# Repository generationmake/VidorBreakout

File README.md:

# VidorBreakout
Breakout board for the Mini PCIe connector of the Arduino MKR Vidor 4000.

## PCB

### Top

### Bot

## License

This hardware is licensed under the CERN OHL v. 1.2

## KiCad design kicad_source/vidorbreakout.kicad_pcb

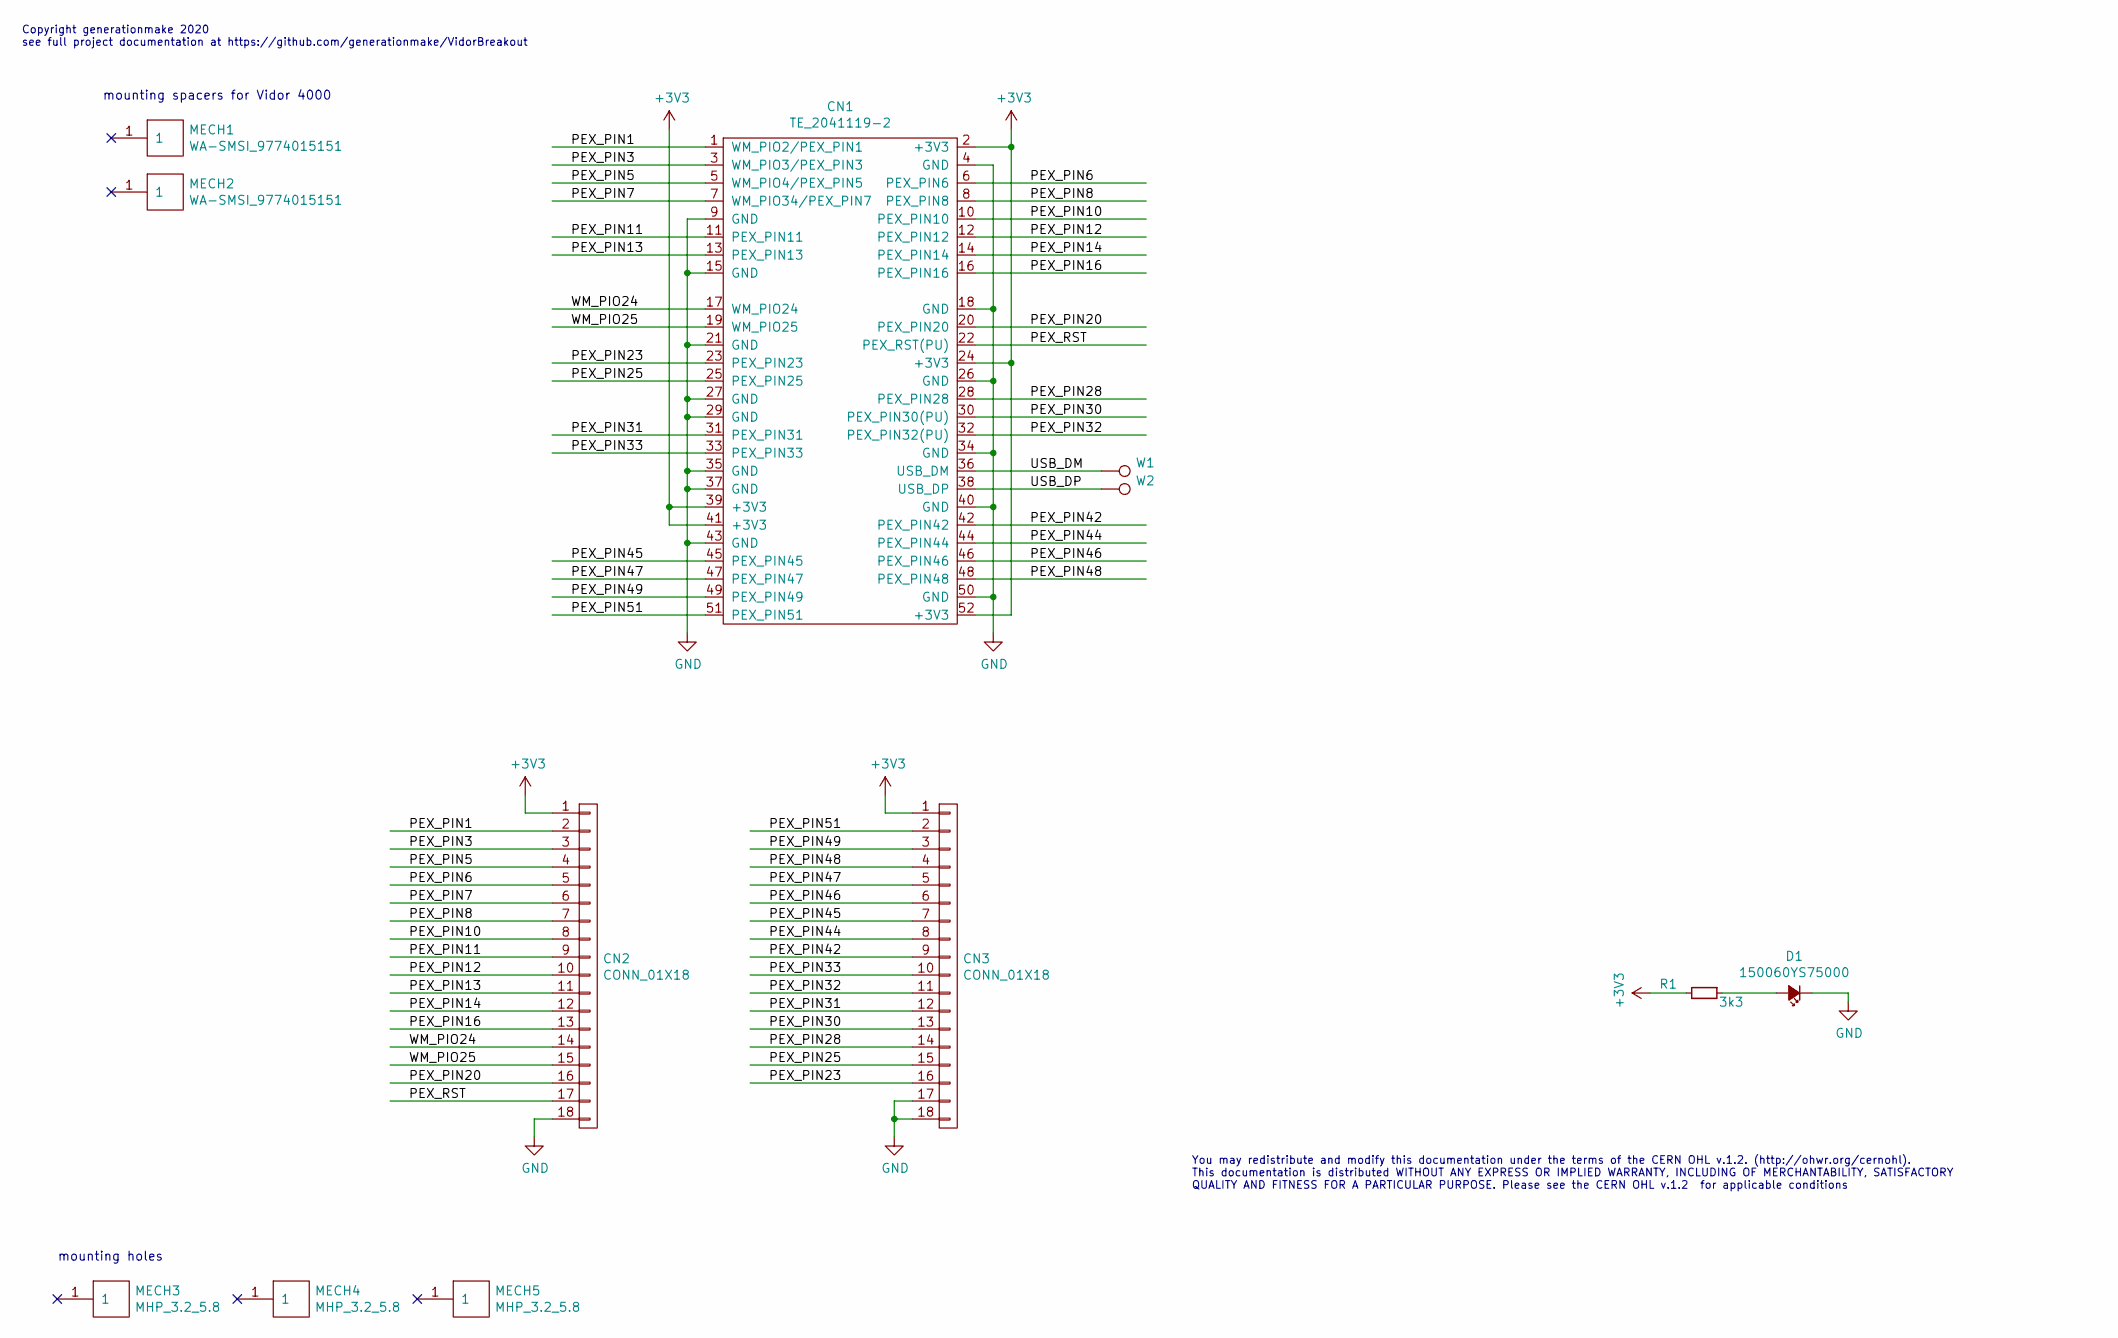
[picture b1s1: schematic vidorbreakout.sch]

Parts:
CN1: TE_2041119-2; MPCIe_4mm
CN2, CN3: CONN_01X18; Pin_Header_Straight_1x18
D1: 150060YS75000; LED_0603
MECH1, MECH2: WA-SMSI_9774015151
MECH3, MECH4, MECH5: MHP_3.2_5.8
R1: 3k3; R_0603
W1, W2: TEST_1P; SolderWirePad_single_1mmSMD

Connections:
+3V3: CN1.2 (+3V3), CN1.24 (+3V3), CN1.39 (+3V3), CN1.41 (+3V3), CN1.52 (+3V3), CN2.1, CN3.1, R1.2
/PEX_PIN1: CN1.1 (WM_PIO2/PEX_PIN1), CN2.2
/PEX_PIN3: CN1.3 (WM_PIO3/PEX_PIN3), CN2.3
/PEX_PIN5: CN1.5 (WM_PIO4/PEX_PIN5), CN2.4
/PEX_PIN6: CN1.6 (PEX_PIN6), CN2.5
/PEX_PIN7: CN1.7 (WM_PIO34/PEX_PIN7), CN2.6
/PEX_PIN8: CN1.8 (PEX_PIN8), CN2.7
/PEX_PIN10: CN1.10 (PEX_PIN10), CN2.8
/PEX_PIN11: CN1.11 (PEX_PIN11), CN2.9
/PEX_PIN12: CN1.12 (PEX_PIN12), CN2.10
/PEX_PIN13: CN1.13 (PEX_PIN13), CN2.11
/PEX_PIN14: CN1.14 (PEX_PIN14), CN2.12
/PEX_PIN16: CN1.16 (PEX_PIN16), CN2.13
/PEX_PIN20: CN1.20 (PEX_PIN20), CN2.16
/PEX_PIN23: CN1.23 (PEX_PIN23), CN3.16
/PEX_PIN25: CN1.25 (PEX_PIN25), CN3.15
/PEX_PIN28: CN1.28 (PEX_PIN28), CN3.14
/PEX_PIN30: CN1.30 (PEX_PIN30(PU)), CN3.13
/PEX_PIN31: CN1.31 (PEX_PIN31), CN3.12
/PEX_PIN32: CN1.32 (PEX_PIN32(PU)), CN3.11
/PEX_PIN33: CN1.33 (PEX_PIN33), CN3.10
/PEX_PIN42: CN1.42 (PEX_PIN42), CN3.9
/PEX_PIN44: CN1.44 (PEX_PIN44), CN3.8
/PEX_PIN45: CN1.45 (PEX_PIN45), CN3.7
/PEX_PIN46: CN1.46 (PEX_PIN46), CN3.6
/PEX_PIN47: CN1.47 (PEX_PIN47), CN3.5
/PEX_PIN48: CN1.48 (PEX_PIN48), CN3.4
/PEX_PIN49: CN1.49 (PEX_PIN49), CN3.3
/PEX_PIN51: CN1.51 (PEX_PIN51), CN3.2
/PEX_RST: CN1.22 (PEX_RST(PU)), CN2.17
/USB_DM: CN1.36 (USB_DM), W1.1
/USB_DP: CN1.38 (USB_DP), W2.1
/WM_PIO24: CN1.17 (WM_PIO24), CN2.14
/WM_PIO25: CN1.19 (WM_PIO25), CN2.15
GND: CN1.4 (GND), CN1.9 (GND), CN1.15 (GND), CN1.18 (GND), CN1.21 (GND), CN1.26 (GND), CN1.27 (GND), CN1.29 (GND), CN1.34 (GND), CN1.35 (GND), CN1.37 (GND), CN1.40 (GND), CN1.43 (GND), CN1.50 (GND), CN2.18, CN3.17, CN3.18, D1.1 (K)
unnamed: D1.2 (A), R1.1

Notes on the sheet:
mounting spacers for Vidor 4000
mounting holes
You may redistribute and modify this documentation under the terms of the CERN OHL v.1.2. (http://ohwr.org/cernohl). This documentation is distributed WITHOUT ANY EXPRESS OR IMPLIED WARRANTY, INCLUDING OF MERCHANTABILITY, SATISFACTORY QUALITY AND FITNESS FOR A PARTICULAR PURPOSE. Please see the CER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
Copyright generationmake 2020 see full project documentation at https://github.com/generationmake/VidorBreakout

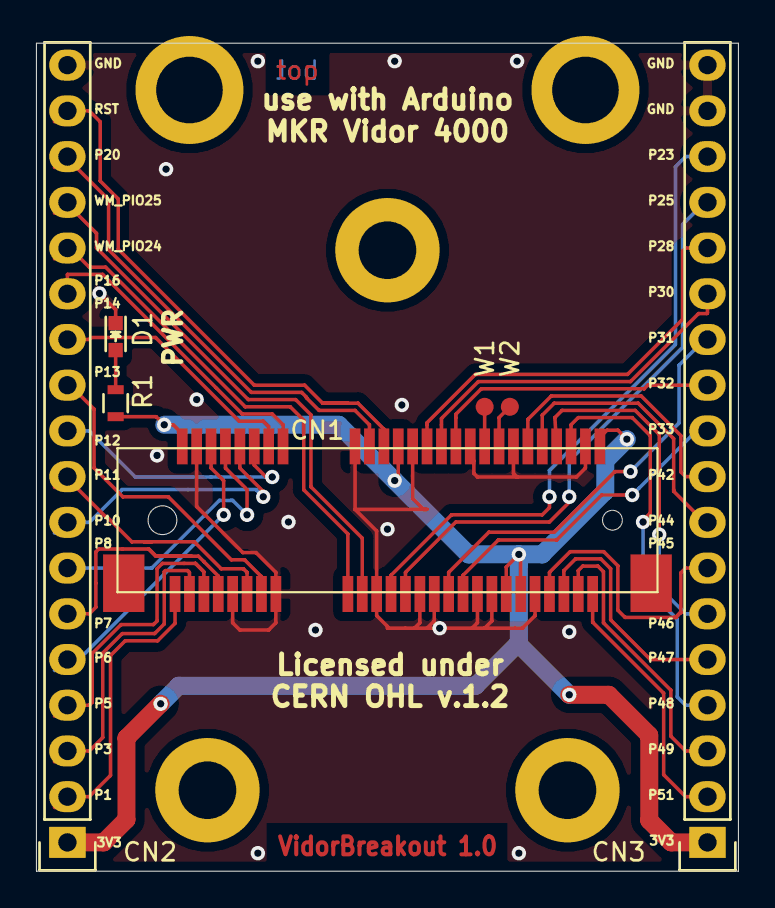
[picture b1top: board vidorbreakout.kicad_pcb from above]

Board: 2 copper layers, 39.0 x 46.0 mm, 12 parts (0 on the bottom side), 36 nets.

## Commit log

2020-02-24 added kicad project
2020-02-24 aligned pin header to grid
2020-02-26 reviewed layout, added silkscreen, updated part values for aisler
2020-02-29 added pin description on bottom silk screen
2020-02-29 added images of pcb
2020-02-29 added pdf schematic
2020-02-29 added licence information
2020-03-15 added license information in schematic and layout, improved silkscreen
2020-03-15 added overview and assembly pdf, updated images

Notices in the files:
kicad_source/vidorbreakout.kicad_pcb:
This documentation describes Open Hardware and is licensed
under the CERN OHL v. 1.2.
kicad_source/vidorbreakout.sch:
This documentation describes Open Hardware and is licensed under the CERN OHL v. 1.2.
